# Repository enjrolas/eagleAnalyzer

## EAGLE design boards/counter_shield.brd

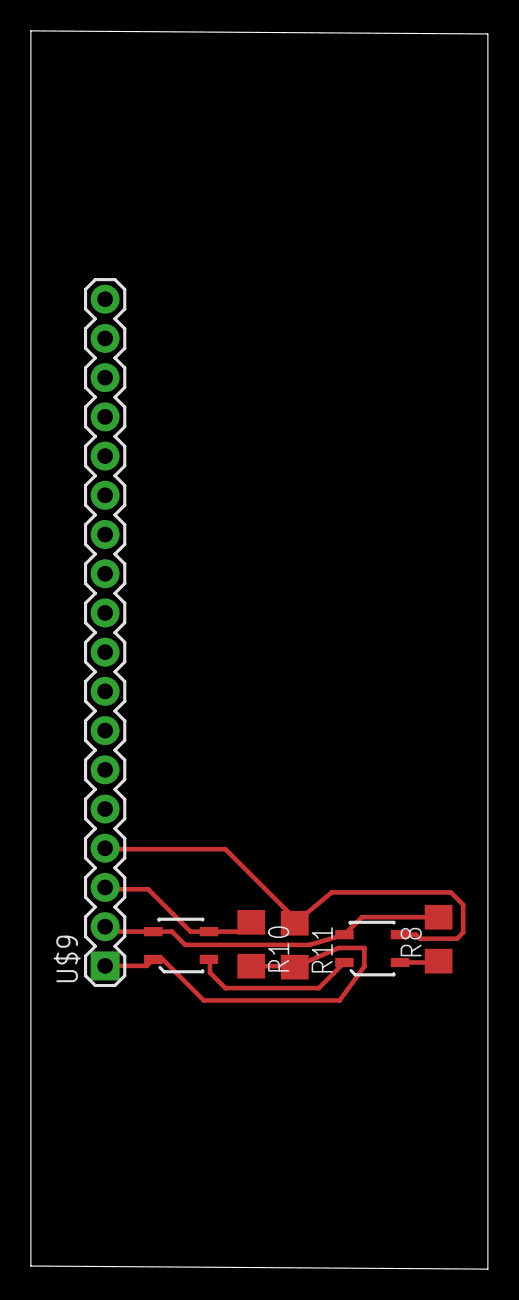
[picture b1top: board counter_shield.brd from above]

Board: 2 copper layers, 29.6 x 80.2 mm, 6 parts (0 on the bottom side), 6 nets.

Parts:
R8: 100; 1206
R10, R11: 10k; 1206
U$6, U$7: QRE1113
U$9: M18_; 1X18

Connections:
GND: R8.2, U$6.4, U$7.4, U$9.2
unnamed: R8.1, U$6.2
unnamed: U$6.1, U$7.2
unnamed: R10.1, U$7.3, U$9.3
unnamed: R11.1, U$6.3, U$9.4
VCC: R10.2, R11.2, U$7.1, U$9.1

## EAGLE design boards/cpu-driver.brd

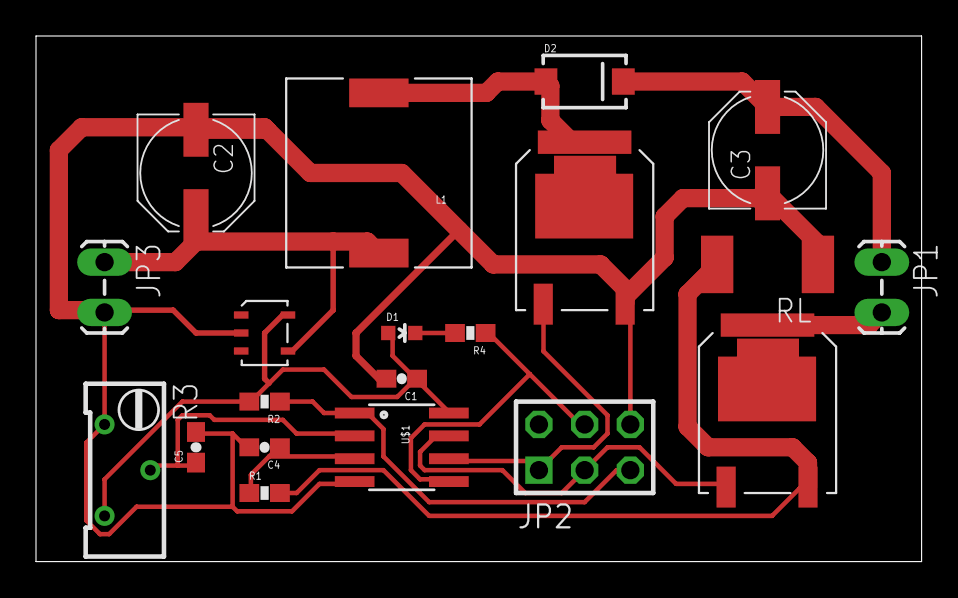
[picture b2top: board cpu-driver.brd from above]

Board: 2 copper layers, 49.2 x 29.2 mm, 20 parts (0 on the bottom side), 14 nets.

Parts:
C1, C5: 1uF; 0603-CAP
C2: 100uF; PANASONIC_D
C3: 330uF; PANASONIC_D
C4: 33uF; 0603-CAP
D1: RED; LED-0603
D2: DIODE-SCHOTTKY_; SMA-DIODE
JP1: BOOST-CONN; 1X02_LOCK_LONGPADS
JP2: AVR-ISP-6
JP3: BATTERY-CONN; 1X02_LOCK_LONGPADS
L1: 180; DR1030
Q1, Q2: RFD14N05L; TO-252AA
R1: 100; 0603-RES
R2: 4k7; 0603-RES
R3: 10k; RTRIM64Y
R4: 220; 0603-RES
RL: 0.2; R2512
U$1: ATTINY13SOIC; SO08
U$2: SOT-23-5

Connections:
BOOST+: C3.+, D2.C, JP1.1
BOOST-: JP1.2, Q2.4
GND: C1.2, C2.-, C3.-, C4.2, C5.2, JP2.6, JP3.2, Q1.3, R3.1, RL.1, U$1.4, U$2.2
MISO: JP2.1, Q1.1, U$1.6
MOSI: JP2.4, R4.1, U$1.5
unnamed: D1.C, R4.2
unnamed: D2.A, L1.2, Q1.4
unnamed: Q2.3, R1.2, RL.2
PB3: C5.1, R3.2, U$1.2
PB4: C4.1, R1.1, U$1.3
RES: JP2.5, R2.1, U$1.1
SCK: JP2.3, Q2.1, U$1.7
VBATT: C2.+, JP3.1, L1.1, U$2.4
VCC: C1.1, D1.A, R2.2, R3.3, U$1.8, U$2.5

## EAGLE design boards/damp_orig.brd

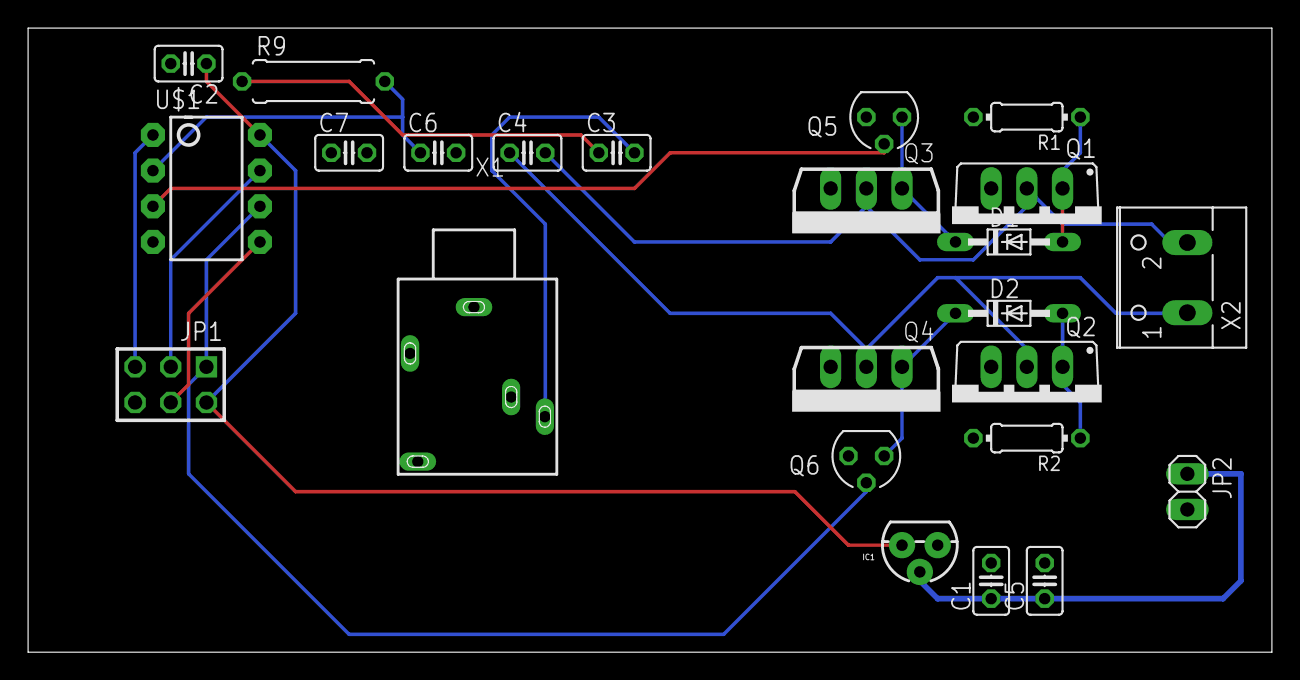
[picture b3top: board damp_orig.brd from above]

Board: 2 copper layers, 88.6 x 44.4 mm, 24 parts (0 on the bottom side), 17 nets.

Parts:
C1, C2: 100nF; C025-025X050
C3: 10uF; C025-025X050
C4, C7: 47nF; C025-025X050
C5: 330uF; C025-025X050
C6: 1nF; C025-025X050
D1, D2: BZX90; DO34Z7
IC1: 78L33 or 7805; TO-92
JP1: AVR-ISP-6VERT; AVR-ISP-6
JP2: 1X02
Q1, Q2: IRF9Z14; TO220BV
Q3, Q4: IRFZ14; TO262-V
Q5, Q6: BS170; SOT54E
R1, R2: 1k; 0204/7
R9: 10k; 0309/10
U$1: ATTINY45DIP8; DIP08
X1: 1503_09
X2: W237-102

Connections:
+12V: C1.1, C5.1, IC1.2, JP2.1, Q1.S, Q2.S, R1.2, R2.2
GND: C1.2, C2.2, C5.2, C6.2, C7.2, IC1.1, JP1.6, JP2.2, Q3.3, Q4.3, Q5.S, Q6.S, U$1.4, X1.1
unnamed: D1.A, Q1.G, R1.1
unnamed: D2.A, Q2.G, R2.1
unnamed: C4.2, Q1.D, Q3.2, X2.2
unnamed: JP1.5, U$1.1
unnamed: C4.1, Q2.D, Q4.2, X2.1
unnamed: D1.C, Q3.1, Q5.D
unnamed: D2.C, Q4.1, Q6.D
unnamed: C6.1, R9.2, U$1.2
unnamed: JP1.4, U$1.5
unnamed: C2.1, IC1.3, JP1.2, U$1.8
unnamed: JP1.1, Q6.G, U$1.6
unnamed: JP1.3, U$1.7
unnamed: C3.1, R9.1
unnamed: Q5.G, U$1.3
unnamed: C3.2, X1.3

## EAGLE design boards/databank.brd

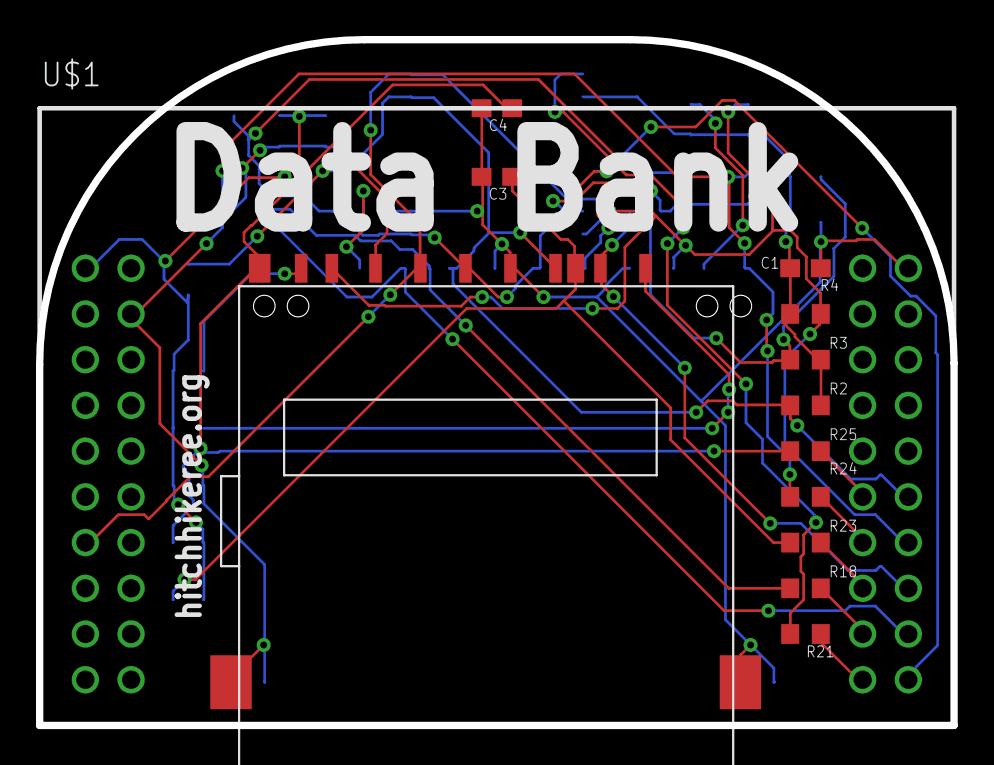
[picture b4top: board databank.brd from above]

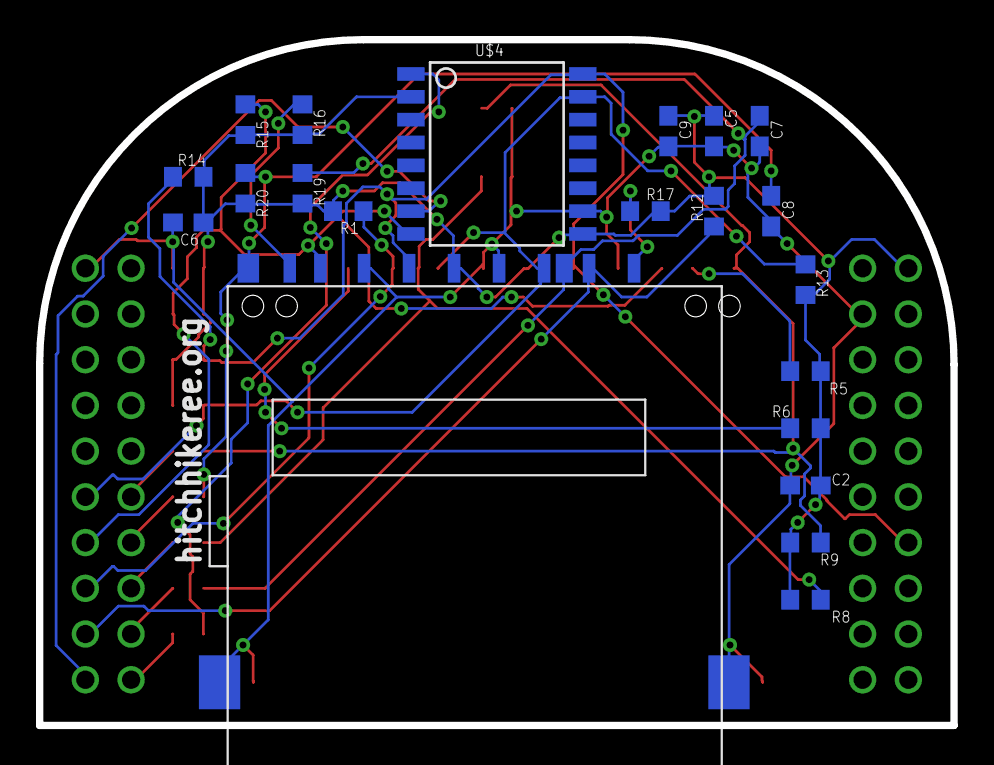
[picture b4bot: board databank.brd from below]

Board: 2 copper layers, 50.8 x 38.1 mm, 34 parts (21 on the bottom side), 22 nets.

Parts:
C1, C3, C4, C5, C7, C8, C9: 0.1u; C0603
C2, C6: 10u; C0603
R1, R2, R3, R4, R5, R6, R8, R9, R12, R13, R14, R15, R16, R17, R19, R20: 10K; R0603
R18, R21, R23, R24, R25: 33; R0603
U$1: LAUNCHPAD_BOOSTER_PACK
U$2, U$3: 101-00405-75
U$4: SO-16LD

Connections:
+3V3: C1.1, C2.1, C5.1, C6.1, C9.1, R1.2, R2.2, R3.2, R4.2, R5.2, R6.2, R8.2, R9.2, R12.2, R13.2, R14.2, R15.2, R16.2, R17.2, R19.2, R20.2, U$1.VCC, U$2.4, U$3.4, U$4.2, U$4.9
FLASH_!CS: U$1.GPIO@6, U$4.7
FLASH_!HOLD: R21.1, U$4.1
GND: C1.2, C2.2, C3.2, C4.2, C5.2, C6.2, C7.2, C8.2, C9.2, U$1.GND@1, U$1.GND@2, U$2.3, U$2.6, U$2.G1$GND, U$2.G2$GND, U$3.3, U$3.6, U$3.G1$GND, U$3.G2$GND, U$4.10
MISO: R4.1, R15.1, U$1.SPIB_SOMI/I2C_SCL, U$2.7, U$3.7, U$4.8
MOSI: R2.1, R13.1, U$1.SPIB_SIMO/I2C_SDA, U$2.2, U$3.2, U$4.15
unnamed: R16.1, U$3.8
unnamed: R17.1, U$3.9
unnamed: R5.1, U$2.8
unnamed: R6.1, U$2.9
unnamed: R21.2, U$1.TIM@10
unnamed: R18.2, U$1.TIM@9
unnamed: R23.2, U$1.TIM@8
unnamed: R24.2, U$1.TIM@7
unnamed: R25.2, U$1.TIM@6
SCLK: R3.1, R14.1, U$1.SPIB_SCLK, U$2.5, U$3.5, U$4.16
SD0_!CD: C3.1, R8.1, R23.1, U$2.CD
SD0_!CS: R1.1, U$1.GPIO@4, U$2.1
SD0_!WP: C4.1, R9.1, R25.1, U$2.WP
SD1_!CD: C7.1, R18.1, R19.1, U$3.CD
SD1_!CS: R12.1, U$1.GPIO@5, U$3.1
SD1_!WP: C8.1, R20.1, R24.1, U$3.WP

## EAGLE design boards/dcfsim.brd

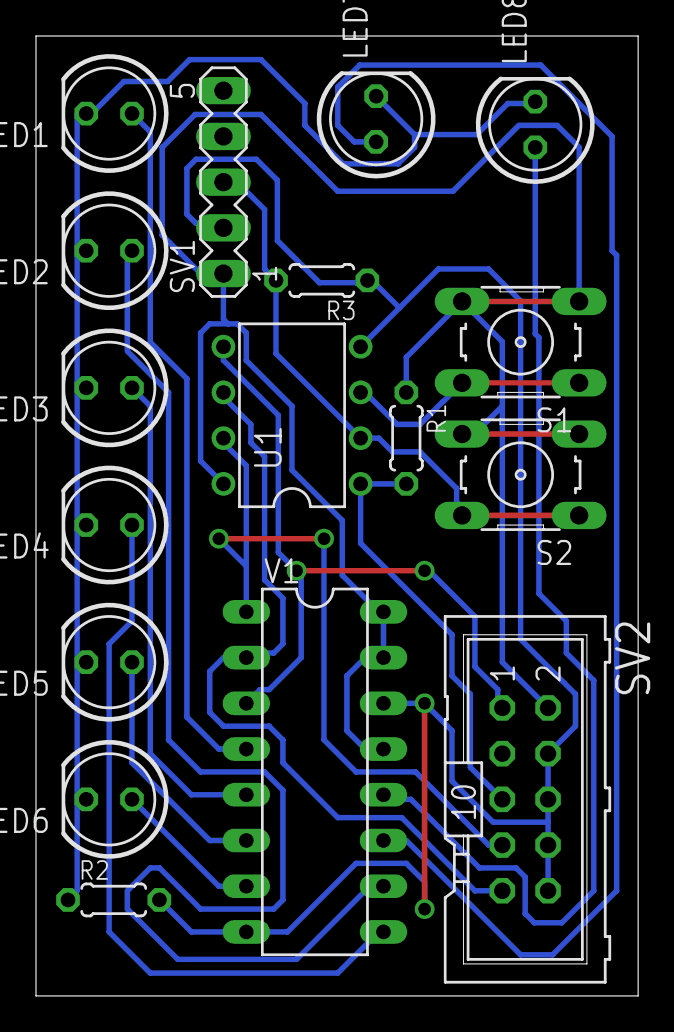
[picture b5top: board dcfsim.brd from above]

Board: 2 copper layers, 33.5 x 53.3 mm, 17 parts (0 on the bottom side), 17 nets.

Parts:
LED1: TIME1; LED5MM
LED2: TIME2; LED5MM
LED3: TIME4; LED5MM
LED4: TIME8; LED5MM
LED5: TIME16; LED5MM
LED6: TIME32; LED5MM
LED7: TIME TYPE 1; LED5MM
LED8: TIME TYPE 2; LED5MM
R1, R3: 10k; 0204/5
R2: 250; 0204/5
S1: CHANGE; B3F-10XX
S2: SET; B3F-10XX
SV1: DCF; MA05-1
SV2: ISP; ML10
U1: ATTINY45-20P; PDIP08_300MIL
V1: 744724N; DIL16

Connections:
+5V: R1.1, S1.3, S1.4, S2.3, S2.4, SV1.1, SV2.2, U1.8, V1.13, V1.15, V1.16
GND: R2.2, R3.1, SV1.2, SV2.4, SV2.6, SV2.8, SV2.10, U1.4, V1.8, V1.14
unnamed: R1.2, SV2.5, U1.1
unnamed: SV2.7, U1.7, V1.1
unnamed: SV2.9, U1.6, V1.2
unnamed: SV2.1, U1.5, V1.3
unnamed: R3.2, S2.1, S2.2, SV1.3, U1.2
unnamed: LED1.A, V1.4
unnamed: LED2.A, V1.10
unnamed: LED4.A, V1.9
unnamed: LED6.A, V1.7
unnamed: LED5.A, V1.6
unnamed: LED3.A, V1.5
unnamed: S1.1, S1.2, U1.3
unnamed: LED7.A, V1.11
unnamed: LED8.A, V1.12
RROU: LED1.K, LED2.K, LED3.K, LED4.K, LED5.K, LED6.K, LED7.K, LED8.K, R2.1

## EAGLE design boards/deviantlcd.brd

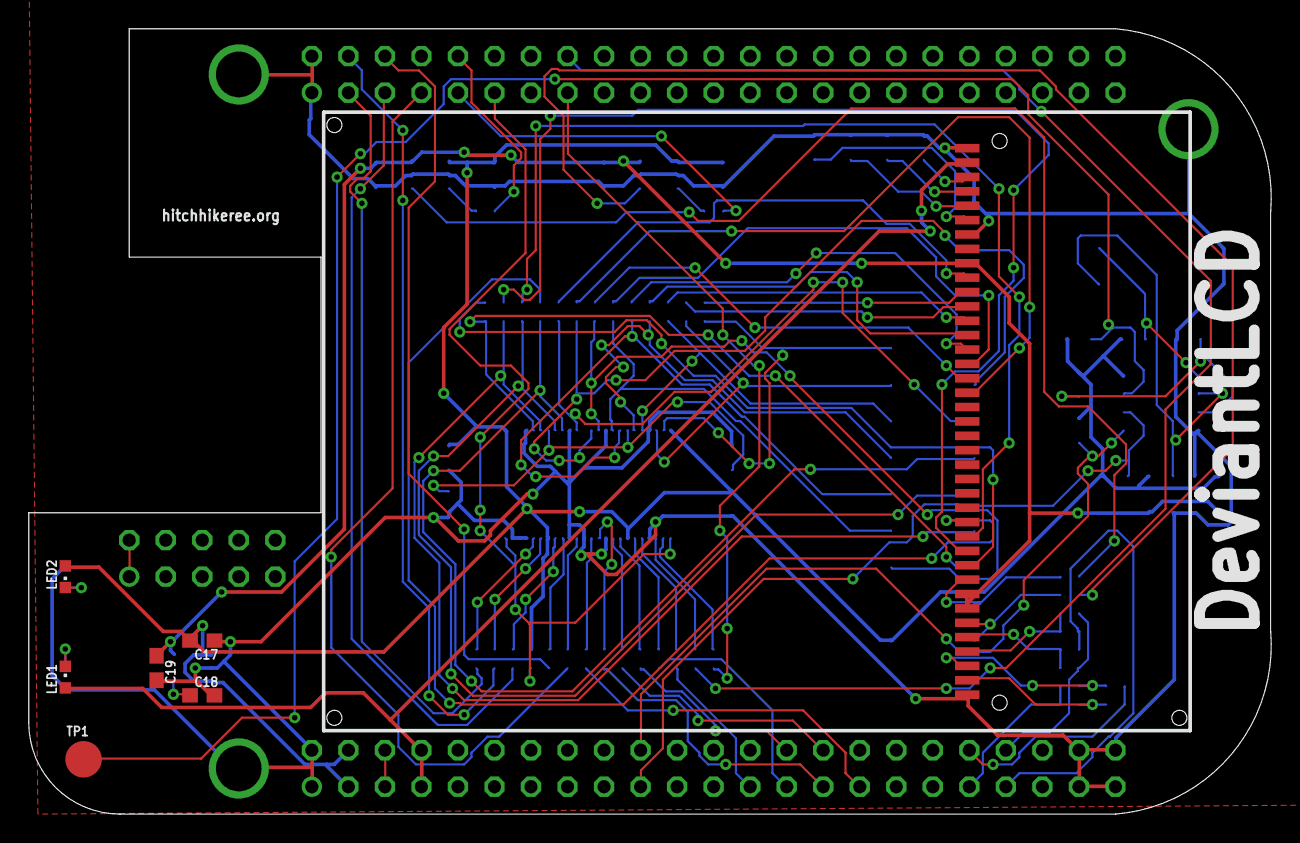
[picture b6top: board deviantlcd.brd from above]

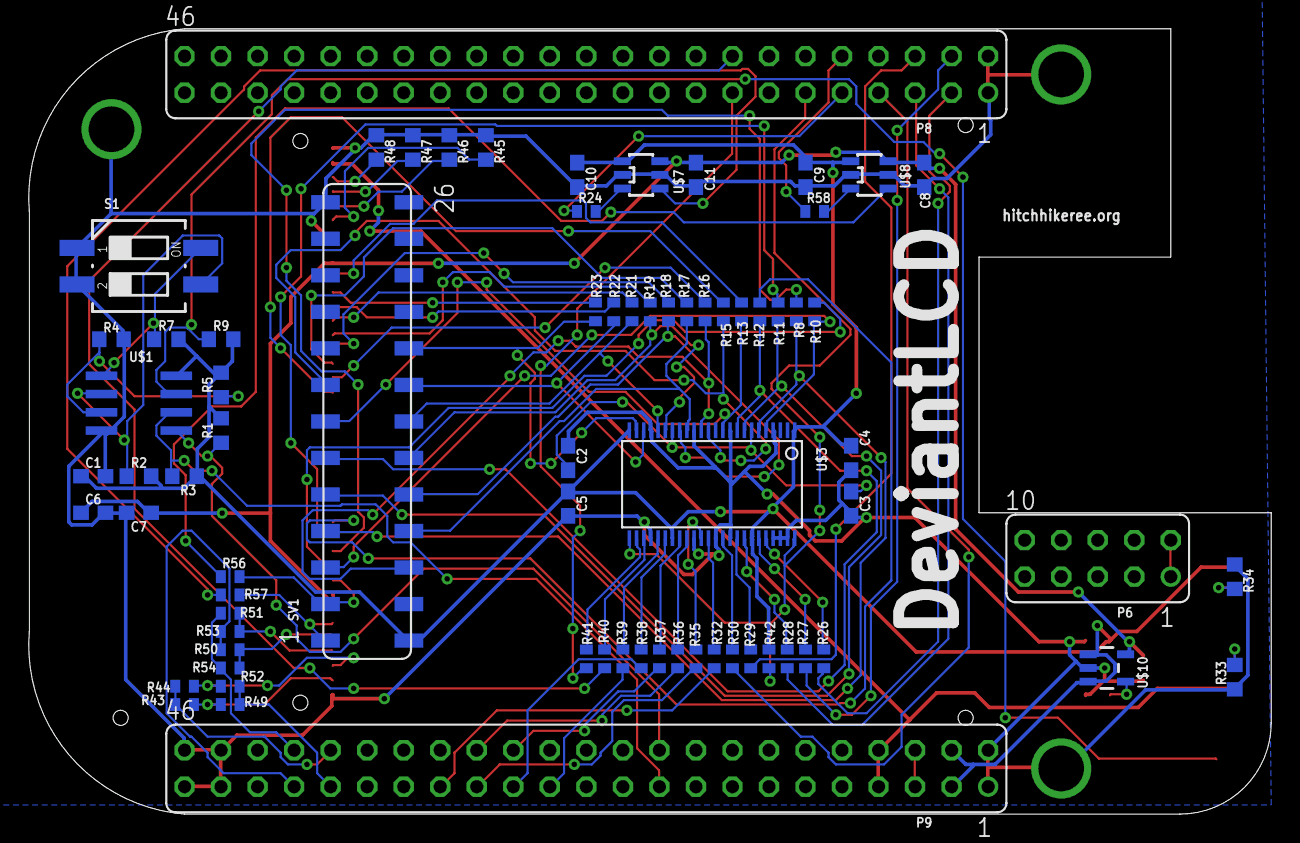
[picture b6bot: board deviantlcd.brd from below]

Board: 2 copper layers, 86.4 x 54.6 mm, 83 parts (73 on the bottom side), 89 nets.

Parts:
C1, C2, C3, C4, C5, C7, C8, C9, C10, C11: 0.1u; C0603
C6: 10u; C0603
C17, C19: 1u; C0603
C18: 10n; C0603
H1, H3, H4: HOLE
LED1: blue; CHIPLED_0603
LED2: green; CHIPLED_0603
P6: FE05-2
P8, P9: FE23-2
R1, R3: 5.6K, 5%; R0603
R2, R5, R7: 4.75K; R0603
R4: 4.75K, DNI; R0603
R8, R10, R11, R12, R13, R15, R16, R17, R18, R19, R21, R22, R23, R24, R26, R27, R28, R29, R30, R32, R35, R36, R37, R38, R39, R40, R41, R56, R57, R58: 33; R0402
R9: 10K; R0603
R33, R45, R46, R47, R48: 150; R0603
R34: 50; R0603
R42: 10K; R0402
R43, R52, R53, R54: 0,DNI; R0402
R44, R49, R50, R51: 0; R0402
S1: 219-02; CTS-219-02
SV1: FE13-2
TP1: TPB2,54; B2,54
U$1: SOIC8
U$3: TSSOP48
U$4: NHD-2.4-240320SF-CTXI
U$7, U$8: SOT23-6
U$10: SOT23-5

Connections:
2.85V: C6.1, C7.1, C8.1, C11.1, C19.1, U$4.7, U$4.8, U$4.31, U$7.6, U$8.6, U$10.5
+3V3: C1.1, C4.1, C5.1, C9.1, C10.1, C17.1, LED2.A, P9.3, P9.4, R1.2, R2.2, R3.2, R5.2, R7.2, R9.2, R42.2, SV1.2, U$1.8, U$3.1, U$3.24, U$3.31, U$3.42, U$7.1, U$8.1, U$10.1, U$10.3
+5V: LED1.A, P9.7, P9.8, U$4.38
AIN0: P9.39, R50.2, R53.2
AIN1: P9.40, R51.2, R54.2
AIN2: P9.37, R49.2, R52.2
AIN3: P9.38, R43.2, R44.2
BAT: P6.1, P6.2
GND: C1.2, C2.2, C3.2, C4.2, C5.2, C6.2, C7.2, C8.2, C9.2, C10.2, C11.2, C17.2, C18.2, C19.2, H1.GND, H3.GND, H4.GND, P8.1, P8.2, P9.1, P9.2, P9.43, P9.44, P9.45, P9.46, R4.1, R33.1, R34.1, R45.1, R46.1, R47.1, R48.1, S1.1, S1.2, SV1.25, U$1.4, U$3.4, U$3.10, U$3.15, U$3.21, U$3.28, U$3.34, U$3.37, U$3.39, U$3.45, U$3.46, U$3.47, U$4.1, U$4.33, U$4.39, U$7.2, U$7.5, U$8.2, U$8.5, U$10.2
GPIO1_2: P8.5, R28.1
GPIO1_3: P8.6, R29.1
GPIO1_6: P8.3, R26.1
GPIO1_7: P8.4, R27.1
GPIO1_13: P8.11, R42.1, U$3.25, U$3.48
GPIO1_14: P8.16, R40.1
GPIO1_15: P8.15, R41.1
GPIO3_19: P9.27, R38.1
GPIO3_21: P9.25, R39.1
I2C2_SCL: P9.19, R3.1, U$1.6
I2C2_SDA: P9.20, R1.1, U$1.5
LCD_CS: R10.1, SV1.5, U$3.5
LCD_DB8: R15.1, SV1.15, U$3.13
LCD_DB9: R16.1, SV1.6, U$3.14
LCD_DB10: R17.1, SV1.8, U$3.16
LCD_DB11: R18.1, SV1.10, U$3.17
LCD_DB12: R19.1, SV1.12, U$3.19
LCD_DB13: R21.1, SV1.14, U$3.20
LCD_DB14: R22.1, SV1.16, U$3.22
LCD_DB15: R23.1, SV1.18, U$3.23
LCD_FMARK: R56.2, SV1.3, U$4.9
LCD_ID: R57.2, SV1.1, U$4.6
LCD_RD: R12.1, SV1.11, U$3.9
LCD_RESET: R13.1, SV1.13, U$3.11
LCD_RS: R8.1, SV1.7, U$3.6
LCD_WR: R11.1, SV1.9, U$3.8
unnamed: R7.1, S1.4, U$1.1
unnamed: R2.1, S1.3, U$1.2
unnamed: R4.2, R5.1, U$1.3
unnamed: R9.1, TP1.TP, U$1.7
unnamed: LED1.C, R33.2
unnamed: LED2.C, R34.2
unnamed: R24.2, U$7.3
unnamed: R58.2, U$8.3
unnamed: R26.2, U$3.44
unnamed: R27.2, U$3.43
unnamed: R28.2, U$3.41
unnamed: R29.2, U$3.40
unnamed: R30.2, U$3.38
unnamed: R32.2, U$3.36
unnamed: R35.2, U$3.35
unnamed: R36.2, U$3.33
unnamed: R37.2, U$3.32
unnamed: R38.2, U$3.30
unnamed: R39.2, U$3.29
unnamed: R40.2, U$3.27
unnamed: R41.2, U$3.26
unnamed: R57.1, U$7.4
unnamed: R56.1, U$8.4
unnamed: R10.2, U$4.10
unnamed: R8.2, U$4.11
unnamed: R11.2, U$4.12
unnamed: R12.2, U$4.13
unnamed: R13.2, U$4.30
unnamed: R23.2, U$4.29
unnamed: R22.2, U$4.28
unnamed: R21.2, U$4.27
unnamed: R19.2, U$4.26
unnamed: R18.2, U$4.25
unnamed: R17.2, U$4.24
unnamed: R16.2, U$4.23
unnamed: R15.2, U$4.22
unnamed: C18.1, U$10.4
unnamed: R45.2, U$4.34
unnamed: R46.2, U$4.35
unnamed: R47.2, U$4.36
unnamed: R48.2, U$4.37
unnamed: R43.1, R49.1, U$4.2
unnamed: R44.1, R52.1, U$4.3
unnamed: R51.1, R53.1, U$4.4
unnamed: R50.1, R54.1, U$4.5
SPI1_CS0: P9.28, R37.1
SPI1_D0: P9.29, R35.1
SPI1_D1: P9.30, R36.1
SPI1_SCLK: P9.31, R32.1
TIMER4: P8.7, R30.1
TIMER5: P8.9, R24.1
TIMER6: P8.10, R58.1
VCCB@2: C2.1, C3.1, U$3.7, U$3.18
VDD: P9.5, P9.6

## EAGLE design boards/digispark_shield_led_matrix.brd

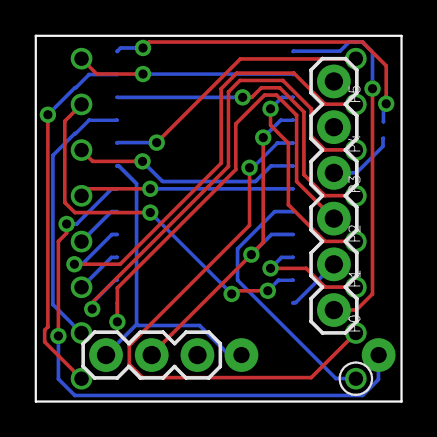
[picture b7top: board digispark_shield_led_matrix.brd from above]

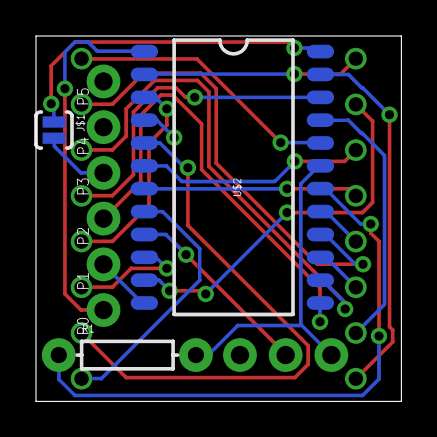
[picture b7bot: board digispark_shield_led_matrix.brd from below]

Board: 2 copper layers, 20.3 x 20.3 mm, 6 parts (3 on the bottom side), 24 nets.

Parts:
J$1: DO; SJ_2S-NO
JP2: 1X03
JP3: 1X06
R1: AXIAL-0.3
U$1: LED_ARRAY_8X8; LED_8X8_2MM_BL-M07C881
U$2: MAX7219; SO-24W

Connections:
GND: JP2.2, U$2.4, U$2.9
unnamed: R1.P$1, U$2.18
unnamed: JP3.1, U$2.1
unnamed: JP3.2, U$2.12
unnamed: JP3.3, U$2.13
unnamed: U$1.-8, U$2.2
unnamed: U$1.-7, U$2.11
unnamed: U$1.-6, U$2.6
unnamed: U$1.-5, U$2.7
unnamed: U$1.-4, U$2.3
unnamed: U$1.-3, U$2.10
unnamed: U$1.-2, U$2.5
unnamed: U$1.-1, U$2.8
unnamed: U$1.+8, U$2.17
unnamed: U$1.+7, U$2.15
unnamed: U$1.+6, U$2.21
unnamed: U$1.+5, U$2.23
unnamed: U$1.+4, U$2.20
unnamed: U$1.+3, U$2.16
unnamed: U$1.+2, U$2.14
unnamed: U$1.+1, U$2.22
unnamed: J$1.1, U$2.24
unnamed: J$1.2, JP3.4
VCC: JP2.3, R1.P$2, U$2.19

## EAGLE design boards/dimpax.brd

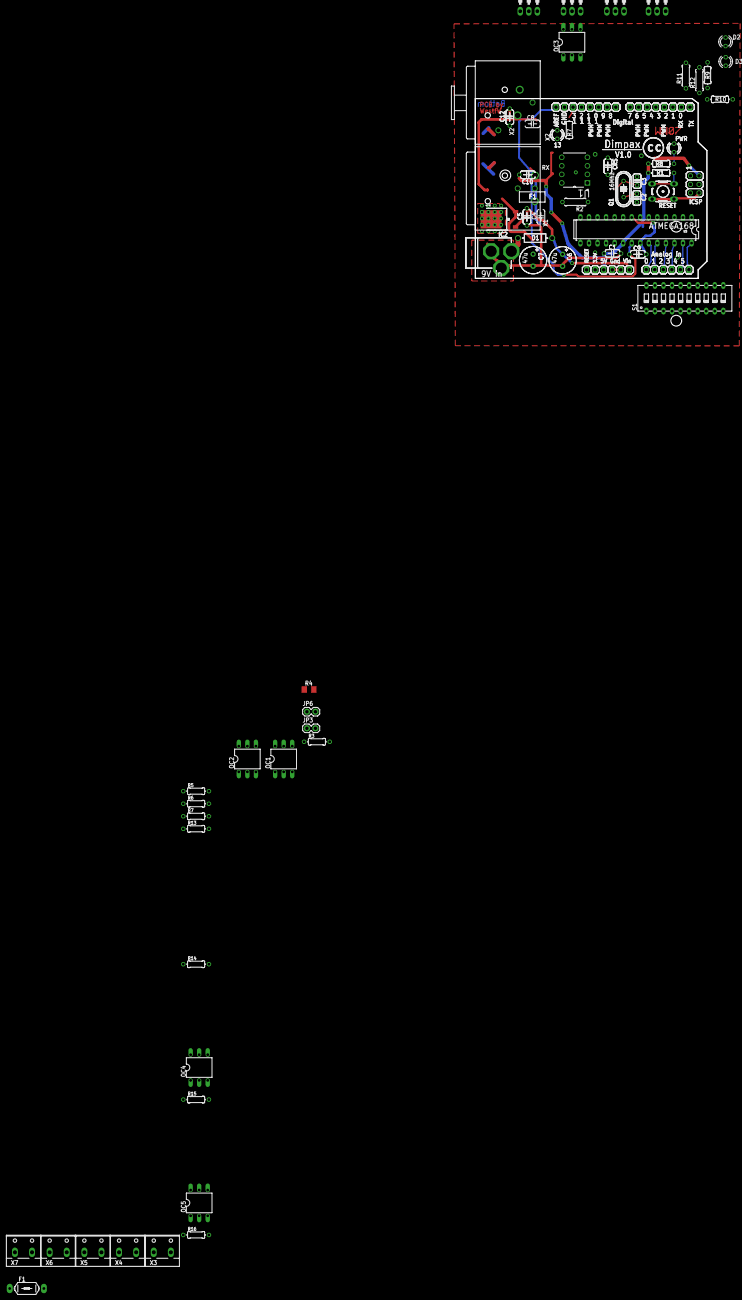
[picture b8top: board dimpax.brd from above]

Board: 2 copper layers, 68.8 x 53.4 mm, 64 parts (1 on the bottom side), 56 nets.

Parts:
C1, C5, C9, C10, C12: 100n; C050-024X044
C2, C3: 22pf; C025-024X044
C6, C7: 47u; E3,5-8
C11: 100n; C1206
CRS: 100n; C050-024X044
D1: 1N4004; DIODE-0.4
D2, D3, D4: LED3MM
DC1: 9V in; DC-21MM
F1: LITTLEFUSE
IC2: 7805DT; TO252
ICSP: ICSP; 2X03
J1, J3: 1X08
J2: 1X06
JP1: 1X06
JP3, JP6: 1X02
OC1: H11A1M; DIL06
OC2, OC3, OC4, OC5: MOC3023M; DIL06
PWR: LED3MM
Q1: 16Mhz; HC49U-V
R1: 10k; 0204/7
R2: 4k7; 0207/7
R3, R9, R10: 1K; 0204/7
R4: 120R; M1206
R5, R14, R15, R16: 180; 0204/7
R6, R7: 15K; 0204/7
R8: 330; 0204/7
R11, R12: 1k; 0207/7
R13: 10K; 0204/7
RESET: B3F-10XX
S1: DIP10YL
T1, T2, T3, T4: BT136; TO220AB
U1: SN75176BP; DIP254P762X508-8
U3: ATMEGA328P_PDIP; DIL28-3
U$3: CC-LOGO
X1: NC3MBH
X2: NC3FAH2
X3, X4, X5, X6, X7: W237-132

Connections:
120V_HOT: F1.1, R5.2, R6.2, R14.2, R15.2, R16.2, T1.2, T2.2, T3.2, T4.2
120V_NEUTRAL: R7.2, X3.1, X4.1, X5.1, X6.1, X7.1
120V_OUT_CH1: T1.1, X4.2
120V_OUT_CH2: T2.1, X5.2
120V_OUT_CH3: T3.1, X6.2
120V_OUT_CH4: T4.1, X7.2
+5V: C1.1, C7.+, C10.2, C11.2, C12.1, IC2.2, ICSP.2, JP1.3, R1.2, R2.1, R8.1, R13.2, U1.8, U3.7, U3.20
A0: J2.1, S1.20, U3.23
A1: J2.2, S1.19, U3.24
A2: J2.3, S1.18, U3.25
A3: J2.4, S1.17, U3.26
A4: J2.5, S1.16, U3.27
A5: J2.6, S1.15, U3.28
AREF: C9.1, J1.8, U3.21
D2: J3.3, U3.4
D3: J3.4, OC1.5, R13.1, U3.5
D4: J3.5, S1.14, U3.6
D7: J3.8, S1.13, U3.13
D8: J1.1, S1.12, U3.14
DMX+: R4.1, U1.6, X1.3, X2.3
DMX-: JP6.2, U1.7, X1.2, X2.2
GND: C1.2, C2.1, C3.1, C5.1, C6.-, C7.-, C9.2, C10.1, C11.1, C12.2, D2.K, D3.K, D4.K, DC1.1, DC1.3, IC2.3, ICSP.6, J1.7, JP1.4, JP1.5, JP3.2, OC1.4, OC2.2, OC3.2, OC4.2, OC5.2, PWR.K, RESET.3, RESET.4, S1.1, S1.2, S1.3, S1.4, S1.5, S1.6, S1.7, S1.8, S1.9, S1.10, U1.2, U1.5, U3.8, U3.22, X1.1, X1.G, X2.1, X2.G
MISO: ICSP.1, J1.5, R3.1, S1.11, U3.18
MOSI: ICSP.4, J1.4, U3.17
unnamed: R2.2, U1.3
unnamed: D4.A, R3.2
unnamed: PWR.A, R8.2
unnamed: R12.2, U1.4
unnamed: OC2.6, R5.1
unnamed: C2.2, Q1.2, U3.9
unnamed: CRS.1, JP3.1
unnamed: D1.A, DC1.2
unnamed: R11.2, U1.1
unnamed: OC1.1, R6.1
unnamed: OC2.4, T1.3
unnamed: OC1.2, R7.1
unnamed: OC3.6, R14.1
unnamed: OC3.4, T2.3
unnamed: OC4.6, R15.1
unnamed: OC4.4, T3.3
unnamed: OC5.6, R16.1
unnamed: OC5.4, T4.3
unnamed: F1.2, X3.2
unnamed: JP6.1, R4.2
unnamed: C3.2, Q1.1, U3.10
unnamed: D3.A, R10.2
unnamed: D2.A, R9.2
PWM5: J3.6, OC2.1, U3.11
PWM6: J3.7, OC3.1, U3.12
PWM9: J1.2, OC4.1, U3.15
PWM10: J1.3, OC5.1, U3.16
RESET: CRS.2, ICSP.5, JP1.1, R1.1, RESET.2, U3.1
RXD: J3.1, R9.1, R11.1, U3.2
SCK: ICSP.3, J1.6, U3.19
TXD: J3.2, R10.1, R12.1, U3.3
VIN: C5.2, C6.+, D1.C, IC2.1, JP1.6

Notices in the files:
boards/digispark_shield_led_matrix.brd:
(C) Sparr 20120824 CC-BY-SA
parts and their libraries:
SparkFun-Sensors: Licensing: CC v3.0 Share-Alike You are welcome to use this library for commercial purposes.
